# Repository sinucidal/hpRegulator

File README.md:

# hpRegulator
5V 2.5A switch-mode voltage regulator based off Micrel chipset

Using an MIC2178-5.0BWM chip from Micrel this circuit should be able to supply up to 2.5 at 5V to feed even the hungriest project.
I developed it for use on a mobile battery pack for a Raspberry Pi rev. 3.0 project that was drawing just under 2A. Right now this 
post will have just the rev. 1.0 information but once I get the board and components I will thoroughly test the system and make
updates to this post accordingly. This file will be the progress log. It should be noted the schematic is based off their data-sheet for the device (http://www.alldatasheet.com/datasheet-pdf/pdf/74541/MICREL/MIC2178-5.0BWM.html), I just gave a component layout and trace routing. I used KiCad 4.0.5 for the project.

"The bigger the sine the louder the whine..." -Sinucidal

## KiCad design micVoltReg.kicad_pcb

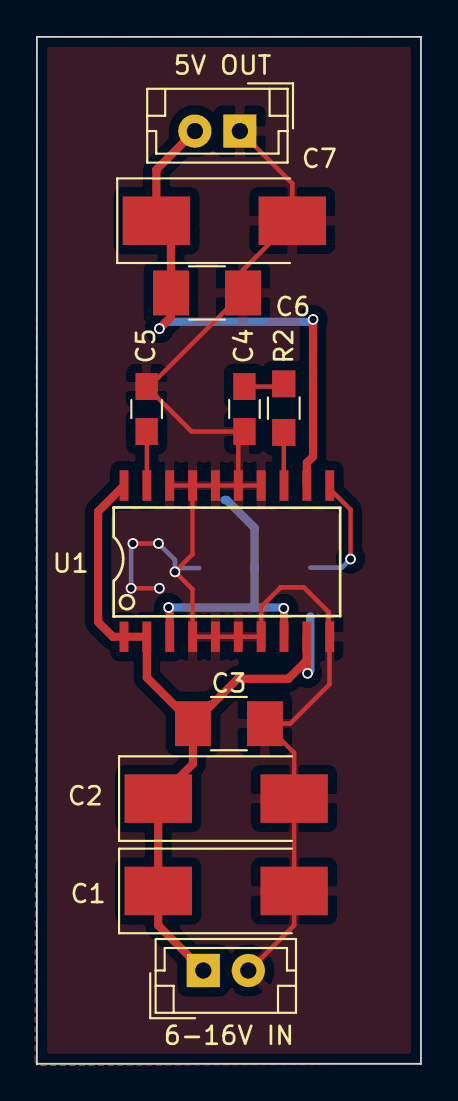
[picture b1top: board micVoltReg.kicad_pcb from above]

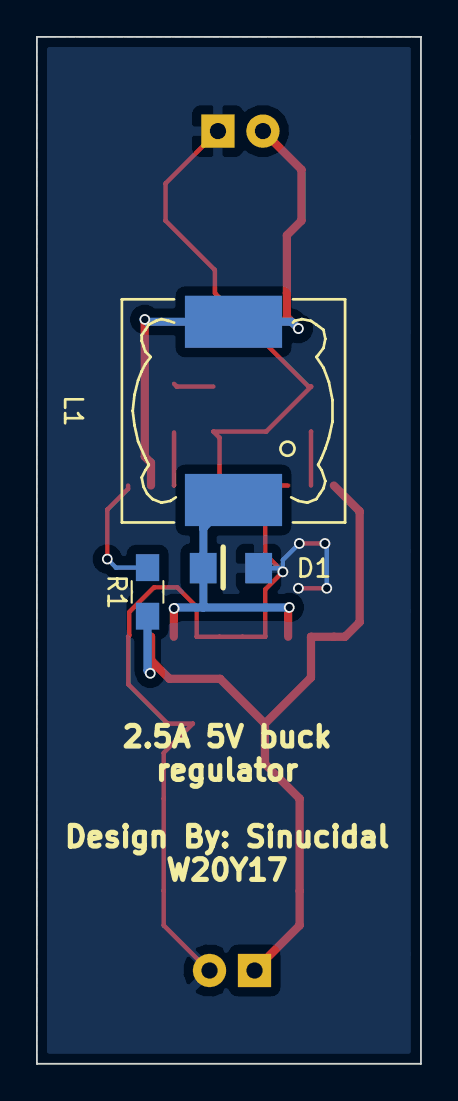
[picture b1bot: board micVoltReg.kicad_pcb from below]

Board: 2 copper layers, 21.3 x 57.0 mm, 14 parts (3 on the bottom side), 8 nets.

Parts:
5V OUT: ouput_conn; JST_EH_B02B-EH-A_02x2.50mm_Straight
6-16V IN: input_conn; JST_EH_B02B-EH-A_02x2.50mm_Straight
C1, C2: 22uF; CP_Tantalum_Case-X_EIA-7343-43_Hand
C3: 0.1uF; C_1210_HandSoldering
C4: 10nF; C_0805_HandSoldering
C5: 0.01uF; C_0805_HandSoldering
C6: 220uF; C_1210_HandSoldering
C7: 220uF; CP_Tantalum_Case-X_EIA-7343-43_Hand
D1: FM5817; DO-214AC
L1: 47uH; Choke_SMD_12x12mm_h6mm
R1: 20k; R_0805_HandSoldering
R2: 15k; R_0805_HandSoldering
U1: MIC2178-5.0BWM; WSOIC-20

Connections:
5v: 5V OUT.2, C6.1, C7.1, L1.2, U1.12
GND: 5V OUT.1, 6-16V IN.2, C1.2, C2.2, C3.2, C4.1, C5.2, C6.2, C7.2, D1.2, U1.4, U1.5, U1.6, U1.7, U1.10, U1.14, U1.15, U1.16, U1.17, U1.18
unnamed: C4.2, R2.2
unnamed: C5.1, U1.19
unnamed: D1.1, L1.1, U1.3, U1.8
unnamed: R1.2, U1.11
unnamed: R2.1, U1.13
VCC: 6-16V IN.1, C1.1, C2.1, C3.1, R1.1, U1.1, U1.2, U1.9, U1.20
